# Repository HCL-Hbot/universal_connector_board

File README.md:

# Healthboth PCB Design
This document outlines the contribution to a PCB design for project Healthbot, which is part of the Health Concept Lab of HAN University of Applied Sciences. It is part of a semester 6 student project including 3 Embedded Systems Engineers and 4 Industrial Design Engineers. The goal for this project was developing a social robot for healthcare, with several functionalities. This PCB is made to be integrated in the robot, but also made quite universal, so it can be used in new robot designs. In the folder media, there are images of the PCB. Because this was a first version, please look at the recommendations below!

## Components
Some components on the PCB that were needed are the I/O Expander, voltage regulators and an UART multiplexer. 
  ### I/O Expander
  Because the GPIO pins of the Pico were completely full and we still needed some, we added an I/O Expander which works with I2C. This expander has 8 I/O channels,   which are also all connected. 
  ### Voltage regulators
  Because of the several needed voltages for the components, two regulators are on the PCB. There is 12 Volt coming in to the PCB via the block terminal. This is     guided to a TSR 1-2433, which converts it to 3.3V. Also a 5V regulator is on the PCB, which was more complicated because it has to have a high output current due   to the ledstrips needing lots of current. 
  ### UART Multiplexer
  The motor driver modules can be controlled via UART communication. Because the Pico doesn't have lots of UART channels, and are already needed for                  communication between the RPI4 and the Pico e.g., an UART Multiplexer was added. Although we don't use it to control our motor drivers, this is still a      possibility because of this multiplexer. This also provided the board with 2 extra UART possibilities for whatever component needs it. 

## !! Issues 
1) The 5V regulator did not work. It is not clear if the regulator wasn't solderded correctly, or the buck converter circuit was not working. Anyways, there was a short between GND and 12V somewhere around the regulator. 
2) Each display needs a identical reset line. The reset line is apparently used to to sync, or atleast stabilize, even though there are seperate chip select lines. 
3) We do not know if the UART multiplexer works, because we don't use it and we needed a pin from the Pico to resolve the previous issue (see Temporary solutions below).

### Temporary solutions
1) Because of safety and time shortage, we just left out the 5V regulator and its circuit that did not work. We now provide 5V via the extra Vcc pins that were added originally as voltage output pins.
2) We used the Pico GPIO pin 21 as extra reset line for the 2nd display. This was originally the 'INH' of the UART Multiplexer. See image below for the connection made. Here can be seen that the trace on the PCB from GPIO21 to the UART Mux was deliberately damaged and replaced with a connection to the reset pin of the 2nd display.

## Recommendations
Below are recommendations for the next group that gets to design a PCB for project Healthbot. These are additions to the previous named issues that need to be adjusted. These recommendations are up to the next developer to decide.

1) Add explicit header pins next to the PICO. This can be useful to easily attach external equipment like a Logic Analyzer or TTL-module, or simply wires to a breadboard if needed. (You can see in the picture of the PCB that we soldered them on for now).
2) Flip the display pin order. This is convenient for testing and prototyping, because the displays can than just be connected (temporarily) to headers on the PCB without the need for several cables. 
3) Add more silk layer documenation. Some of this was already actually done in the design, but some of these labels were skipped during production for some reason. (Also adding small hints for Vcc, gnd and other pins could be useful for connecting the components, when not using JST connectors).
4) Add a working 5V regulator, with enough output current (>6A). Try to not use a regulator that is too small, this was a problem in the first version. 
5) Add status LEDs and just an onboard LED to control.
6) Add a couple of buttons, like to reset the PICO for example. Also, power on/off buttons would be nice (could be tricky for the RPI, but would be useful).

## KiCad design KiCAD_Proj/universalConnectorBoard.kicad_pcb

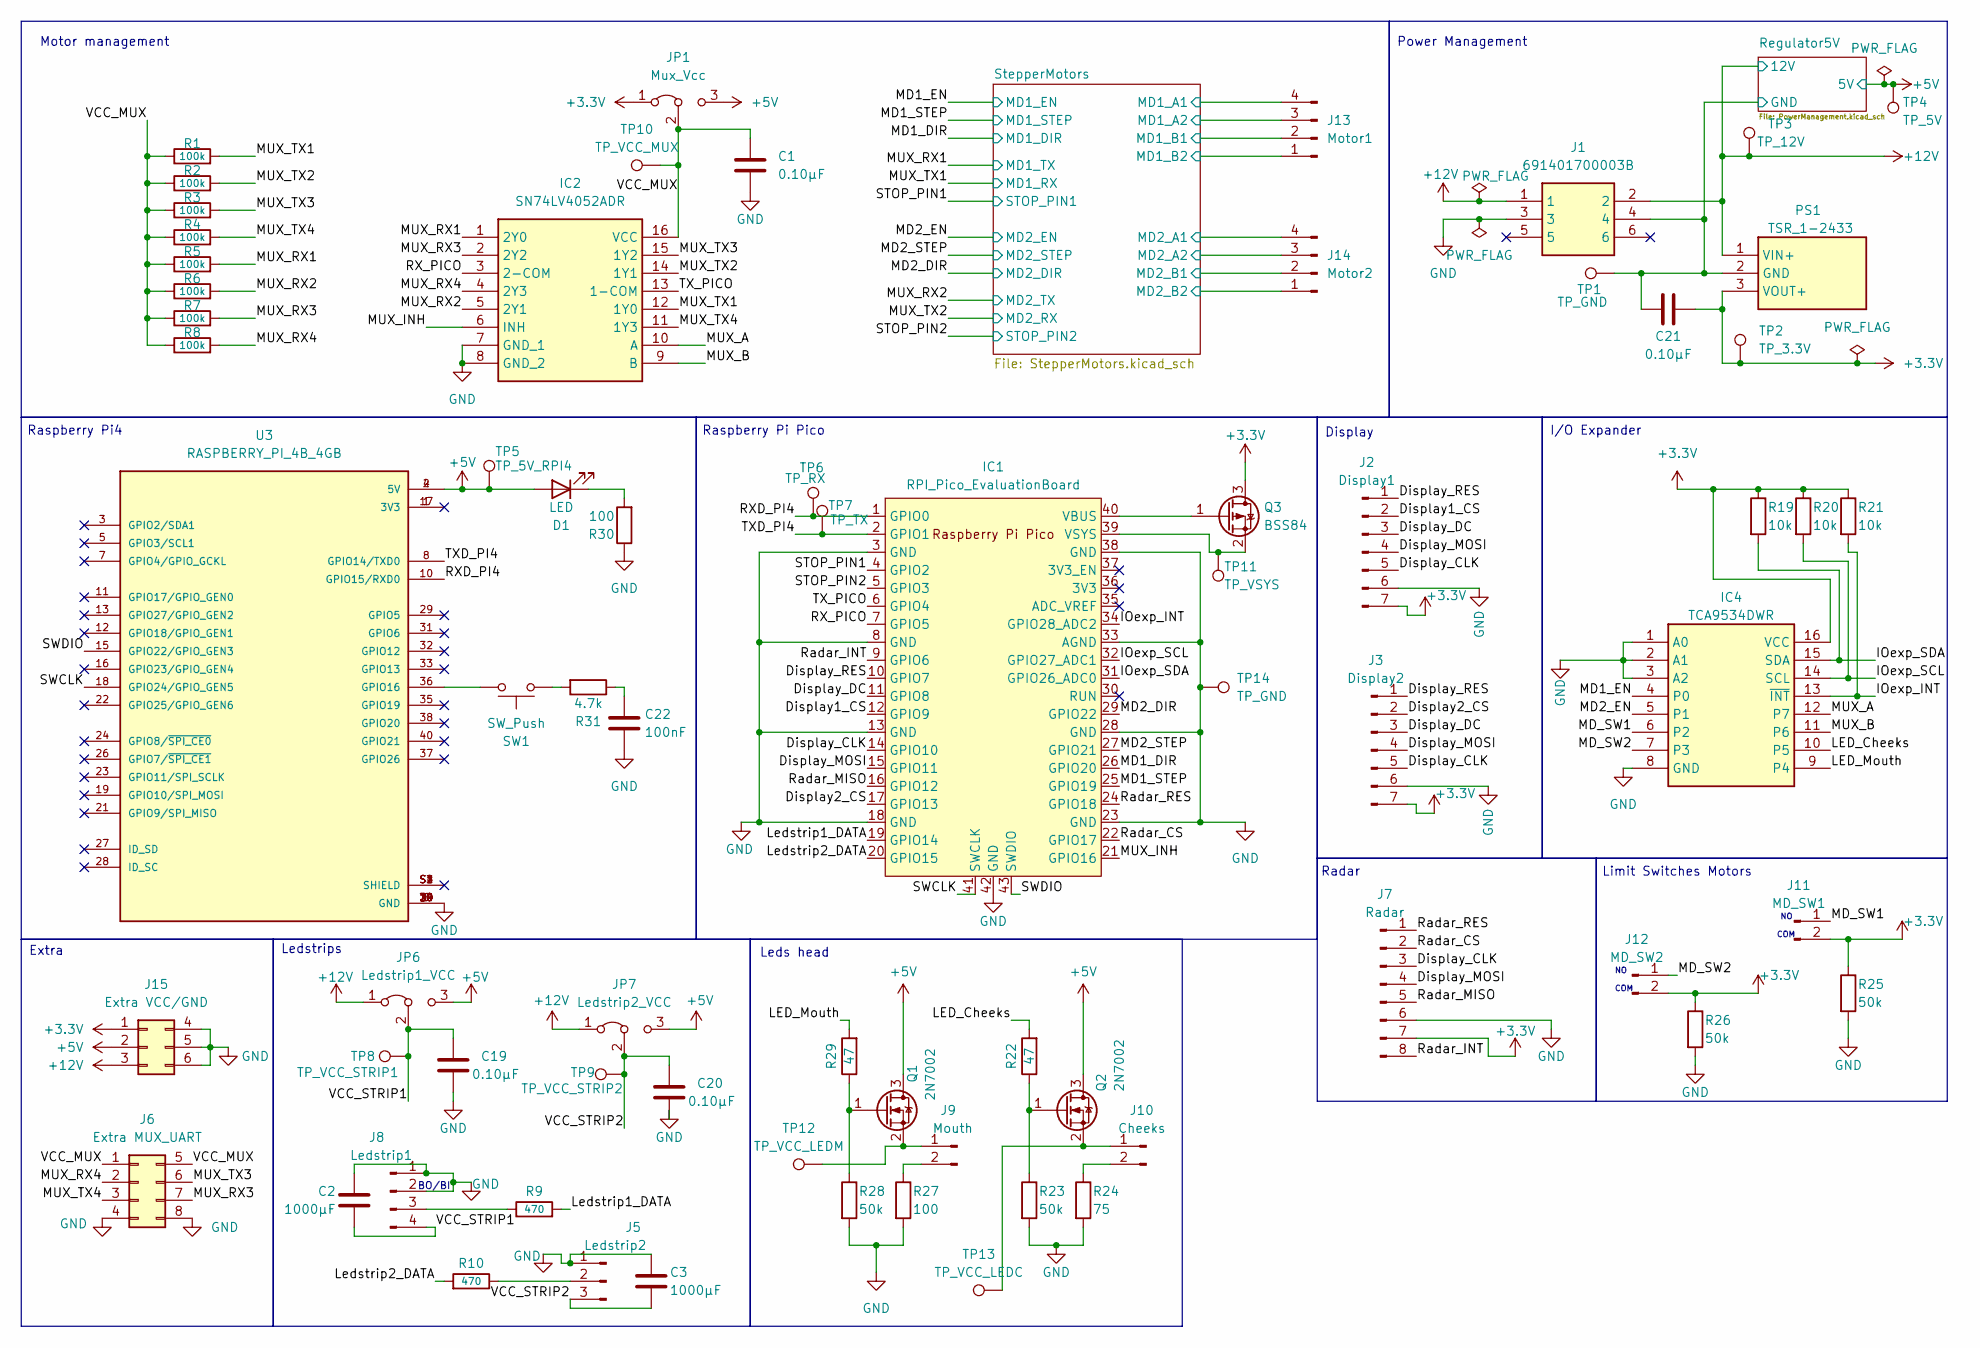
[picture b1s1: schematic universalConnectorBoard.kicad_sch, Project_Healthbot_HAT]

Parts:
C1, C19, C20, C21: 0.10μF; C_0603_1608Metric_Pad1.08x0.95mm_HandSolder
C2, C3: 1000μF; C_0603_1608Metric_Pad1.08x0.95mm_HandSolder
C22: 100nF; C_0603_1608Metric_Pad1.08x0.95mm_HandSolder
D1: LED; LED_0603_1608Metric_Pad1.05x0.95mm_HandSolder
IC1: RPI_Pico_EvaluationBoard; RPi_Pico_SMD_TH
IC2: SN74LV4052ADR; SOIC127P600X175-16N; Mouser Part Number 595-SN74LV4052ADR
IC4: TCA9534DWR; SOIC127P1030X265-16N; Mouser Part Number 595-TCA9534DWR
J1: 691401700003B; Manufacturer_Part_Number 691401700003B
J2: Display1; JST_XH_S7B-XH-A_1x07_P2.50mm_Horizontal
J3: Display2; JST_XH_S7B-XH-A_1x07_P2.50mm_Horizontal
J5: Ledstrip2; JST_XH_S3B-XH-A_1x03_P2.50mm_Horizontal
J6: Extra MUX_UART; PinHeader_2x04_P2.54mm_Vertical
J7: Radar; JST_XH_S8B-XH-A_1x08_P2.50mm_Horizontal
J8: Ledstrip1; JST_XH_S4B-XH-A_1x04_P2.50mm_Horizontal
J9: Mouth; JST_XH_S2B-XH-A_1x02_P2.50mm_Horizontal
J10: Cheeks; JST_XH_S2B-XH-A_1x02_P2.50mm_Horizontal
J11: MD_SW1; JST_XH_S2B-XH-A_1x02_P2.50mm_Horizontal
J12: MD_SW2; JST_XH_S2B-XH-A_1x02_P2.50mm_Horizontal
J13: Motor1; JST_XH_S4B-XH-A_1x04_P2.50mm_Horizontal
J14: Motor2; JST_XH_S4B-XH-A_1x04_P2.50mm_Horizontal
J15: Extra VCC/GND; PinHeader_2x03_P2.54mm_Vertical
JP1: Mux_Vcc; PinHeader_1x03_P2.54mm_Vertical
JP6: Ledstrip1_VCC; PinHeader_1x03_P2.54mm_Vertical
JP7: Ledstrip2_VCC; PinHeader_1x03_P2.54mm_Vertical
PS1: TSR_1-2433; TSR-1-2433; Manufacturer_Part_Number TSR 1-2433
Q1, Q2: 2N7002; SOT-23
Q3: BSS84; SOT-23
R1, R2, R3, R4, R5, R6, R7, R8: 100k; R_0603_1608Metric_Pad0.98x0.95mm_HandSolder
R9, R10: 470; R_0603_1608Metric_Pad0.98x0.95mm_HandSolder
R19, R20, R21: 10k; R_0603_1608Metric_Pad0.98x0.95mm_HandSolder
R22, R29: 47; R_0603_1608Metric_Pad0.98x0.95mm_HandSolder
R23, R25, R26, R28: 50k; R_0603_1608Metric_Pad0.98x0.95mm_HandSolder
R24: 75; R_0603_1608Metric_Pad0.98x0.95mm_HandSolder
R27, R30: 100; R_0603_1608Metric_Pad0.98x0.95mm_HandSolder
R31: 4.7k; R_0603_1608Metric_Pad0.98x0.95mm_HandSolder
SW1: SW_Push; PinHeader_1x02_P2.54mm_Vertical
TP1, TP14: TP_GND; TestPoint_Pad_D1.5mm
TP2: TP_3.3V; TestPoint_Pad_D1.5mm
TP3: TP_12V; TestPoint_Pad_D1.5mm
TP4: TP_5V; TestPoint_Pad_D1.5mm
TP5: TP_5V_RPI4; TestPoint_Pad_D1.5mm
TP6: TP_RX; TestPoint_Pad_D1.5mm
TP7: TP_TX; TestPoint_Pad_D1.5mm
TP8: TP_VCC_STRIP1; TestPoint_Pad_D1.5mm
TP9: TP_VCC_STRIP2; TestPoint_Pad_D1.5mm
TP10: TP_VCC_MUX; TestPoint_Pad_D1.5mm
TP11: TP_VSYS; TestPoint_Pad_D1.5mm
TP12: TP_VCC_LEDM; TestPoint_Pad_D1.5mm
TP13: TP_VCC_LEDC; TestPoint_Pad_D1.5mm
U3: RASPBERRY_PI_4B_4GB; MODULE_RASPBERRY_PI_4B_4GB; PARTREV 4

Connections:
+3.3V: C21.2, IC4.16 (VCC), J2.7, J3.7, J7.7, J11.2, J12.2, J15.1, JP1.1 (A), PS1.3 (VOUT+), Q3.3 (D), R19.1, R20.1, R21.1, R25.1, R26.1, TP2.1; also elsewhere on the board
+5V: D1.2 (A), J15.2, JP1.3 (B), JP6.3 (B), JP7.3 (B), Q1.3 (D), Q2.3 (D), TP4.1, TP5.1, U3.2 (5V), U3.4 (5V); also elsewhere on the board
+12V: J1.1, J1.2, J15.3, JP6.1 (A), JP7.1 (A), PS1.1 (VIN+), TP3.1; also elsewhere on the board
/Display1_CS: IC1.12 (GPIO9), J2.2
/Display2_CS: IC1.17 (GPIO13), J3.2
/Display_CLK: IC1.14 (GPIO10), J2.5, J3.5, J7.3
/Display_DC: IC1.11 (GPIO8), J2.3, J3.3
/Display_MOSI: IC1.15 (GPIO11), J2.4, J3.4, J7.4
/Display_RES: IC1.10 (GPIO7), J2.1, J3.1
/IOexp_INT: IC1.34 (GPIO28_ADC2), IC4.13 (~INT), R21.2
/IOexp_SCL: IC1.32 (GPIO27_ADC1), IC4.14 (SCL), R20.2
/IOexp_SDA: IC1.31 (GPIO26_ADC0), IC4.15 (SDA), R19.2
/LED_Cheeks: IC4.10 (P5), R22.2
/LED_Mouth: IC4.9 (P4), R29.2
/Ledstrip1_DATA: IC1.19 (GPIO14), R9.2
/Ledstrip2_DATA: IC1.20 (GPIO15), R10.2
/MD1_DIR: IC1.26 (GPIO20); also elsewhere on the board
/MD1_EN: IC4.4 (P0); also elsewhere on the board
/MD1_STEP: IC1.25 (GPIO19); also elsewhere on the board
/MD2_DIR: IC1.29 (GPIO22); also elsewhere on the board
/MD2_EN: IC4.5 (P1); also elsewhere on the board
/MD2_STEP: IC1.27 (GPIO21); also elsewhere on the board
/MD_SW1: IC4.6 (P2), J11.1
/MD_SW2: IC4.7 (P3), J12.1
/MUX_A: IC2.10 (A), IC4.12 (P7)
/MUX_B: IC2.9 (B), IC4.11 (P6)
/MUX_INH: IC1.21 (GPIO16), IC2.6 (INH)
/MUX_RX1: IC2.1 (2Y0), R5.2; also elsewhere on the board
/MUX_RX2: IC2.5 (2Y1), R6.2; also elsewhere on the board
/MUX_RX3: IC2.2 (2Y2), J6.7, R7.2
/MUX_RX4: IC2.4 (2Y3), J6.2, R8.2
/MUX_TX1: IC2.12 (1Y0), R1.2; also elsewhere on the board
/MUX_TX2: IC2.14 (1Y1), R2.2; also elsewhere on the board
/MUX_TX3: IC2.15 (1Y2), J6.6, R3.2
/MUX_TX4: IC2.11 (1Y3), J6.3, R4.2
/RXD_PI4: IC1.1 (GPIO0), TP6.1, U3.10 (GPIO15/RXD0)
/RX_PICO: IC1.7 (GPIO5), IC2.3 (2-COM)
/Radar_CS: IC1.22 (GPIO17), J7.2
/Radar_INT: IC1.9 (GPIO6), J7.8
/Radar_MISO: IC1.16 (GPIO12), J7.5
/Radar_RES: IC1.24 (GPIO18), J7.1
/STOP_PIN1: IC1.4 (GPIO2); also elsewhere on the board
/STOP_PIN2: IC1.5 (GPIO3); also elsewhere on the board
/SWCLK: IC1.41 (SWCLK), U3.18 (GPIO24/GPIO_GEN5)
/SWDIO: IC1.43 (SWDIO), U3.15 (GPIO22/GPIO_GEN3)
/StepperMotors/MD1_A1: J13.4; also elsewhere on the board
/StepperMotors/MD1_A2: J13.3; also elsewhere on the board
/StepperMotors/MD1_B1: J13.2; also elsewhere on the board
/StepperMotors/MD1_B2: J13.1; also elsewhere on the board
/StepperMotors/MD2_A1: J14.4; also elsewhere on the board
/StepperMotors/MD2_A2: J14.3; also elsewhere on the board
/StepperMotors/MD2_B1: J14.2; also elsewhere on the board
/StepperMotors/MD2_B2: J14.1; also elsewhere on the board
/TXD_PI4: IC1.2 (GPIO1), TP7.1, U3.8 (GPIO14/TXD0)
/TX_PICO: IC1.6 (GPIO4), IC2.13 (1-COM)
/VCC_MUX: C1.1, IC2.16 (VCC), J6.1, J6.5, JP1.2 (C), R1.1, R2.1, R3.1, R4.1, R5.1, R6.1, R7.1, R8.1, TP10.1
/VCC_STRIP1: C2.2, C19.1, J8.4, JP6.2 (C), TP8.1
/VCC_STRIP2: C3.2, C20.1, J5.3, JP7.2 (C), TP9.1
GND: C1.2, C2.1, C3.1, C19.2, C20.2, C21.1, C22.2, IC1.3 (GND), IC1.8 (GND), IC1.13 (GND), IC1.18 (GND), IC1.23 (GND), IC1.28 (GND), IC1.33 (AGND), IC1.38 (GND), IC1.42 (GND), IC2.7 (GND_1), IC2.8 (GND_2), IC4.1 (A0), IC4.2 (A1), IC4.3 (A2), IC4.8 (GND), J1.3, J1.4, J2.6, J3.6, J5.1, J6.4, J6.8, J7.6, J8.1, J8.2, J15.4, J15.5, J15.6, PS1.2 (GND), R23.2, R24.2, R25.2, R26.2, R27.2, R28.2, R30.1, TP1.1, TP14.1, U3.6 (GND), U3.9 (GND), U3.14 (GND), U3.20 (GND), U3.25 (GND), U3.30 (GND), U3.34 (GND), U3.39 (GND); also elsewhere on the board
unnamed: C22.1, R31.1
unnamed: D1.1 (K), R30.2
unnamed: IC1.40 (VBUS), Q3.1 (G)
unnamed: IC1.39 (VSYS), Q3.2 (S), TP11.1
unnamed: J5.2, R10.1
unnamed: J8.3, R9.1
unnamed: J9.1, Q1.2 (S), TP12.1
unnamed: J9.2, R27.1
unnamed: J10.1, Q2.2 (S), TP13.1
unnamed: J10.2, R24.1
unnamed: Q1.1 (G), R28.1, R29.1
unnamed: Q2.1 (G), R22.1, R23.1
unnamed: R31.2, SW1.1
unnamed: SW1.2, U3.36 (GPIO16)

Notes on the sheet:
Display
Motor management
Raspberry Pi Pico
Power Management
BO/BI
Limit Switches Motors
COM
Raspberry Pi4
Ledstrips
Leds head
Radar
I/O Expander
Extra

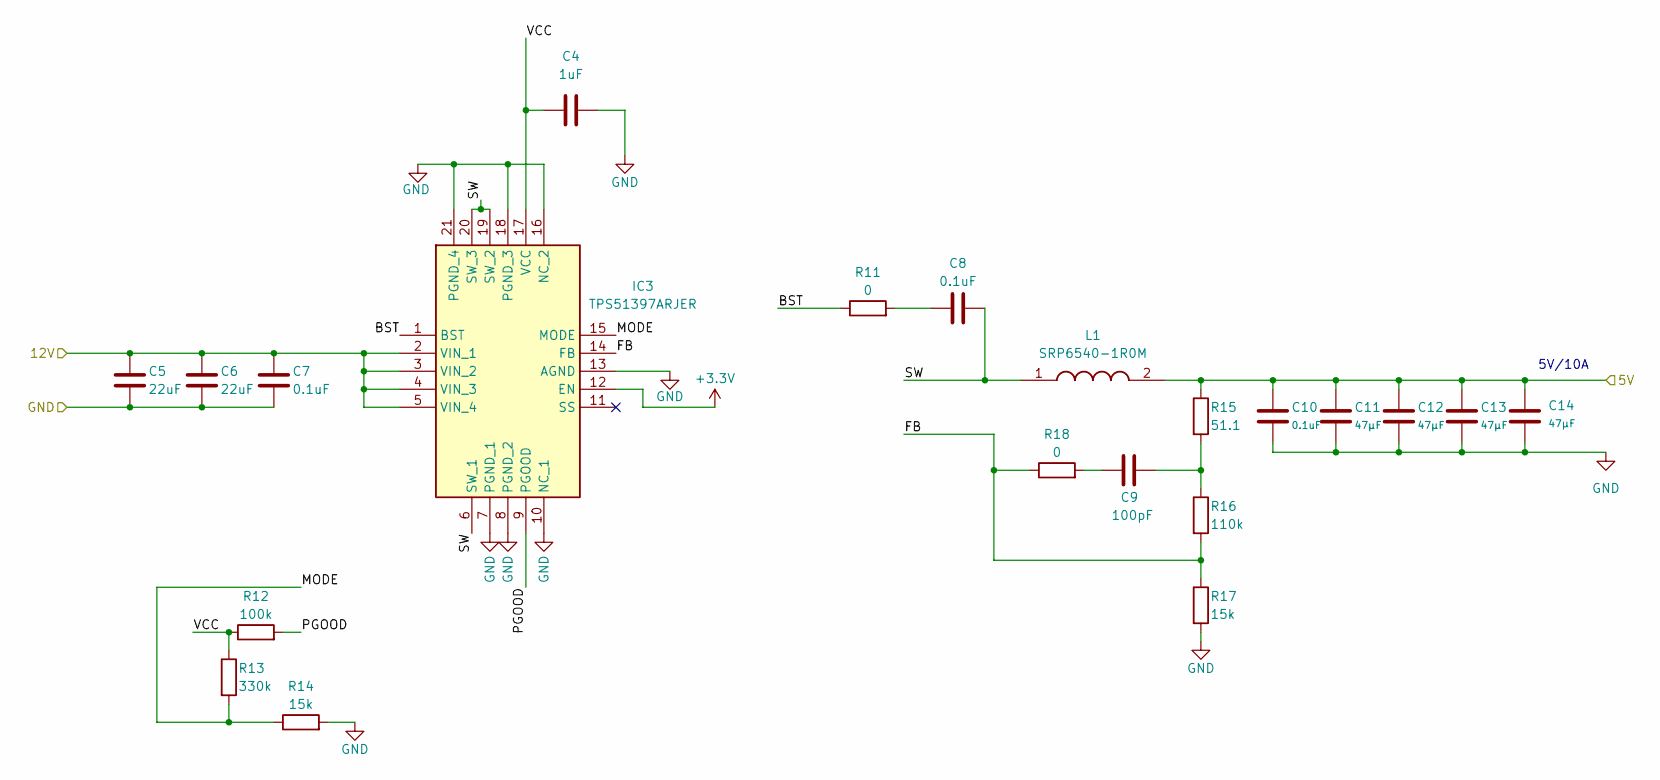
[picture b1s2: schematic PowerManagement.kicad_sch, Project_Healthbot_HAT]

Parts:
C4: 1uF; C_0603_1608Metric_Pad1.08x0.95mm_HandSolder
C5, C6: 22uF; C_0603_1608Metric_Pad1.08x0.95mm_HandSolder
C7, C8, C10: 0.1uF; C_0603_1608Metric_Pad1.08x0.95mm_HandSolder
C9: 100pF; C_0603_1608Metric_Pad1.08x0.95mm_HandSolder
C11, C12, C13, C14: 47µF; C_0603_1608Metric_Pad1.08x0.95mm_HandSolder
IC3: TPS51397ARJER; QFN45P300X300X100-21N-D; Mouser Part Number 595-TPS51397ARJER
L1: SRP6540-1R0M; INDPM7265X400N; Manufacturer_Part_Number SRP6540-1R0M
R11, R18: 0; R_0603_1608Metric_Pad0.98x0.95mm_HandSolder
R12: 100k; R_0603_1608Metric_Pad0.98x0.95mm_HandSolder
R13: 330k; R_0603_1608Metric_Pad0.98x0.95mm_HandSolder
R14, R17: 15k; R_0603_1608Metric_Pad0.98x0.95mm_HandSolder
R15: 51.1; R_0603_1608Metric_Pad0.98x0.95mm_HandSolder
R16: 110k; R_0603_1608Metric_Pad0.98x0.95mm_HandSolder

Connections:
+3.3V: IC3.12 (EN); also elsewhere on the board
+5V: C10.1, C11.1, C12.1, C13.1, C14.1, L1.2, R15.1; also elsewhere on the board
+12V: C5.1, C6.1, C7.1, IC3.2 (VIN_1), IC3.3 (VIN_2), IC3.4 (VIN_3), IC3.5 (VIN_4); also elsewhere on the board
/Regulator5V/BST: IC3.1 (BST), R11.1
/Regulator5V/FB: IC3.14 (FB), R16.2, R17.1, R18.1
/Regulator5V/MODE: IC3.15 (MODE), R13.2, R14.1
/Regulator5V/PGOOD: IC3.9 (PGOOD), R12.2
/Regulator5V/SW: C8.2, IC3.6 (SW_1), IC3.19 (SW_2), IC3.20 (SW_3), L1.1
/Regulator5V/VCC: C4.1, IC3.17 (VCC), R12.1, R13.1
GND: C4.2, C5.2, C6.2, C7.2, C10.2, C11.2, C12.2, C13.2, C14.2, IC3.7 (PGND_1), IC3.8 (PGND_2), IC3.10 (NC_1), IC3.13 (AGND), IC3.16 (NC_2), IC3.18 (PGND_3), IC3.21 (PGND_4), R14.2, R17.2; also elsewhere on the board
unnamed: C8.1, R11.2
unnamed: C9.1, R15.2, R16.1
unnamed: C9.2, R18.2

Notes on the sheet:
5V/10A

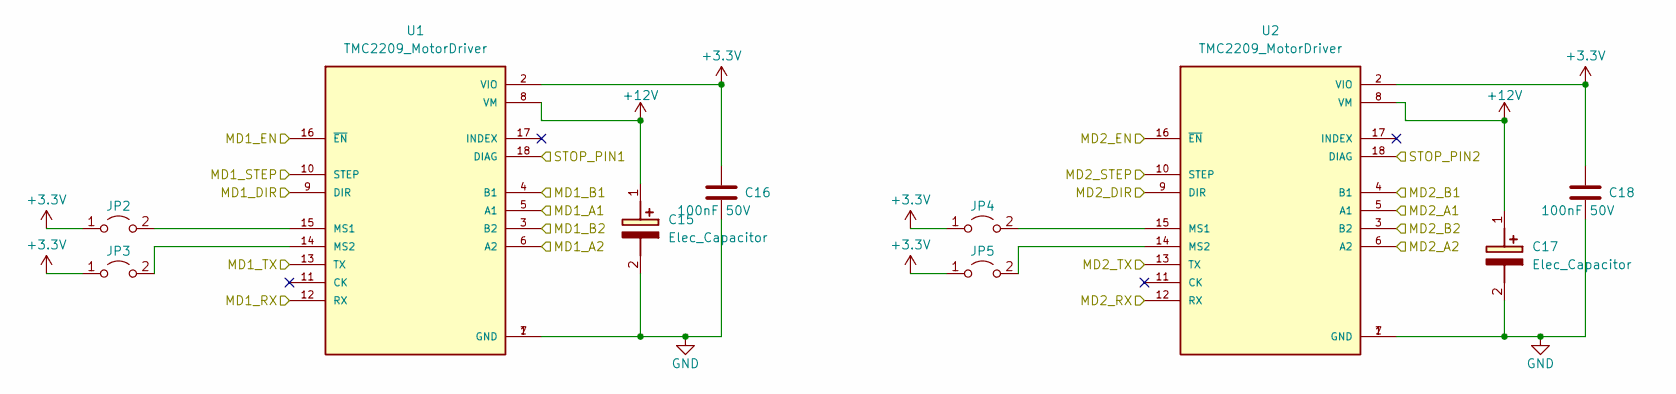
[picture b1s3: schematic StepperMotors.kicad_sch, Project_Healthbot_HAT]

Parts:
C15, C17: Elec_Capacitor; CAPAE1000X1050N; Mouser Part Number 594-MAL214699103E3
C16, C18: 100nF 50V; C_0603_1608Metric_Pad1.08x0.95mm_HandSolder; LCSC C476766
JP2, JP3, JP4, JP5: Jumper_2_Open; SolderJumper-2_P1.3mm_Open_RoundedPad1.0x1.5mm; LCSC x
U1, U2: TMC2209_MotorDriver; MODULE_TMC2209_SILENTSTEPSTICK; PARTREV 1.20

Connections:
+3.3V: C16.1, C18.1, JP2.1 (A), JP3.1 (A), JP4.1 (A), JP5.1 (A), U1.2 (VIO), U2.2 (VIO); also elsewhere on the board
+12V: C15.1 (+), C17.1 (+), U1.8 (VM), U2.8 (VM); also elsewhere on the board
/MD1_DIR: U1.9 (DIR); also elsewhere on the board
/MD1_EN: U1.16 (~EN); also elsewhere on the board
/MD1_STEP: U1.10 (STEP); also elsewhere on the board
/MD2_DIR: U2.9 (DIR); also elsewhere on the board
/MD2_EN: U2.16 (~EN); also elsewhere on the board
/MD2_STEP: U2.10 (STEP); also elsewhere on the board
/MUX_RX1: U1.13 (TX); also elsewhere on the board
/MUX_RX2: U2.13 (TX); also elsewhere on the board
/MUX_TX1: U1.12 (RX); also elsewhere on the board
/MUX_TX2: U2.12 (RX); also elsewhere on the board
/STOP_PIN1: U1.18 (DIAG); also elsewhere on the board
/STOP_PIN2: U2.18 (DIAG); also elsewhere on the board
/StepperMotors/MD1_A1: U1.5 (A1); also elsewhere on the board
/StepperMotors/MD1_A2: U1.6 (A2); also elsewhere on the board
/StepperMotors/MD1_B1: U1.4 (B1); also elsewhere on the board
/StepperMotors/MD1_B2: U1.3 (B2); also elsewhere on the board
/StepperMotors/MD2_A1: U2.5 (A1); also elsewhere on the board
/StepperMotors/MD2_A2: U2.6 (A2); also elsewhere on the board
/StepperMotors/MD2_B1: U2.4 (B1); also elsewhere on the board
/StepperMotors/MD2_B2: U2.3 (B2); also elsewhere on the board
GND: C15.2 (-), C16.2, C17.2 (-), C18.2, U1.1 (GND), U1.7 (GND), U2.1 (GND), U2.7 (GND); also elsewhere on the board
unnamed: JP2.2 (B), U1.15 (MS1)
unnamed: JP3.2 (B), U1.14 (MS2)
unnamed: JP4.2 (B), U2.15 (MS1)
unnamed: JP5.2 (B), U2.14 (MS2)

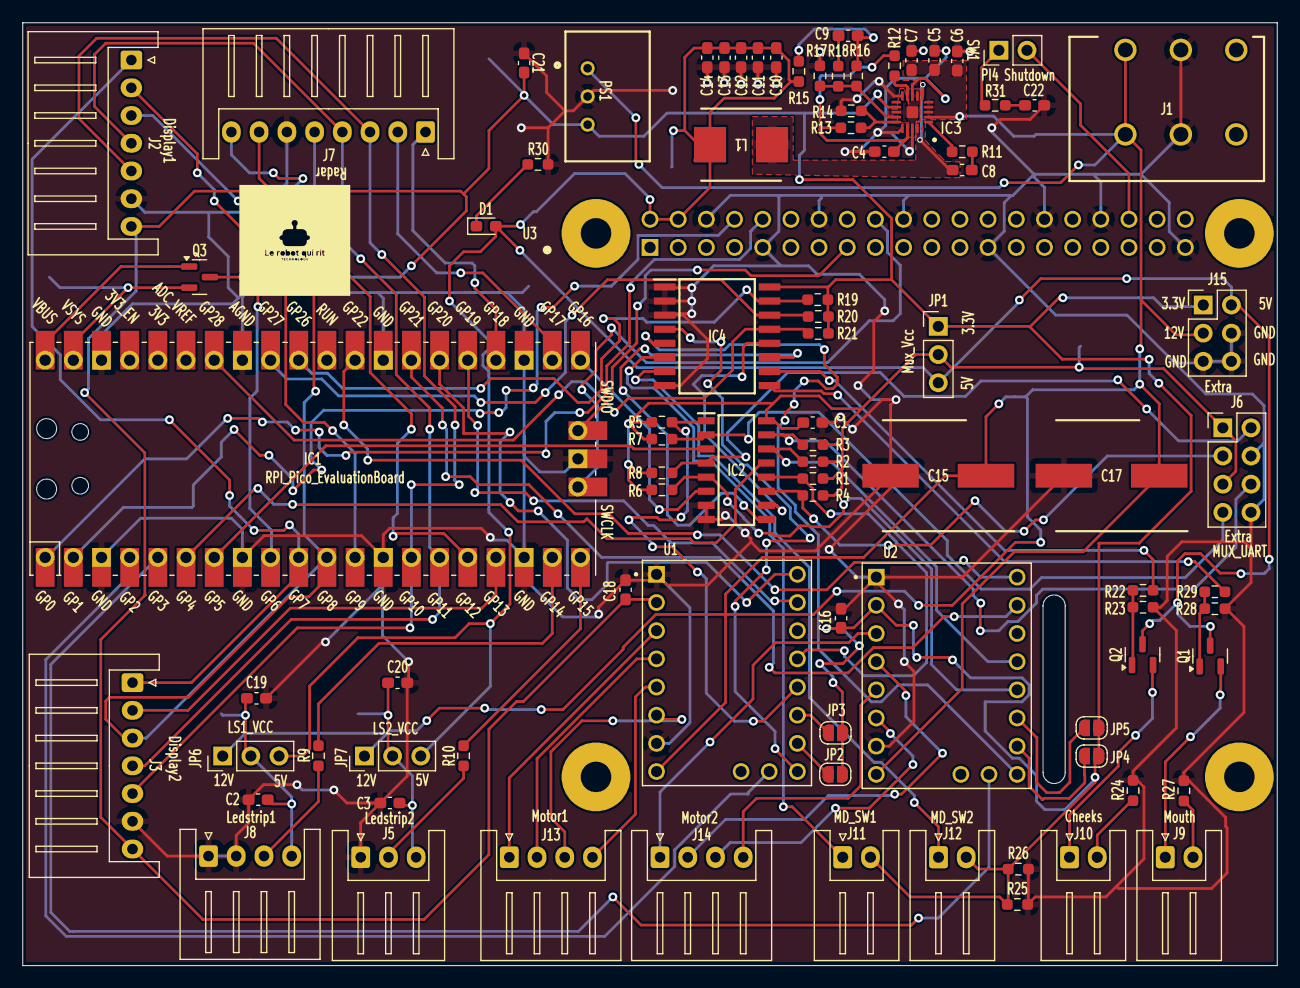
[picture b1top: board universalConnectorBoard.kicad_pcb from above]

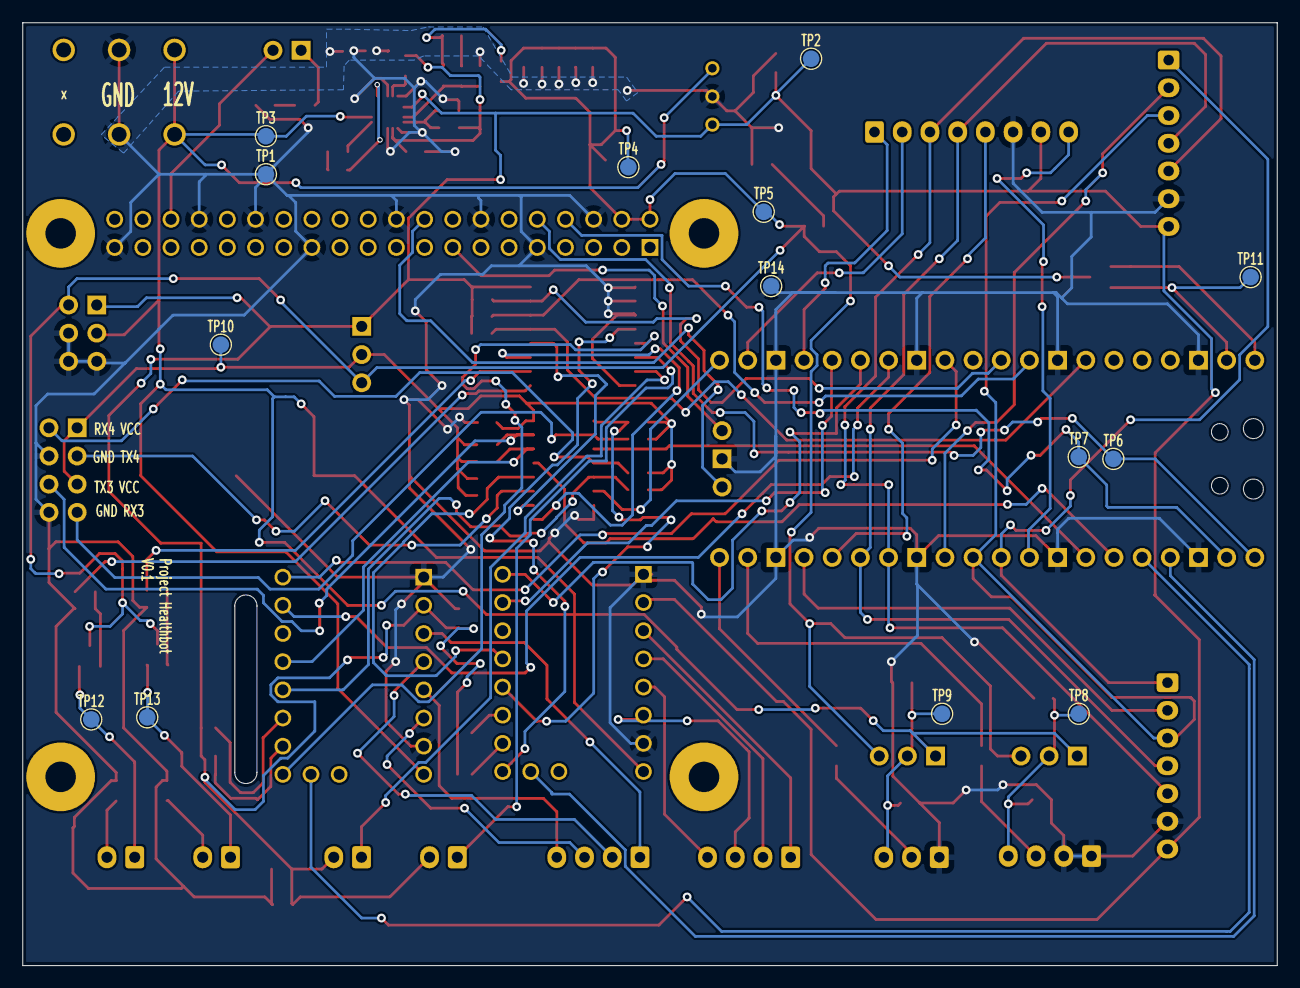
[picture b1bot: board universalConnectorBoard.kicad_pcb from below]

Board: 2 copper layers, 113.1 x 85.0 mm, 103 parts (14 on the bottom side), 86 nets.

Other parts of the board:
Logo: d0ed0aed-a5b7-4fbb-959d-d2596cb26e0d

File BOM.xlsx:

Reference, | Value | , | Datasheet | , | Footprint | , | Qty | , | DNP | , | Beschrijving
C1,C19,C20,C21, | 0.10Î¼F | , | ~ | , | Capacitor_SMD:C_0603_1608Metric_Pad1.08x0.95mm_HandSolder | , | 4 | , |  | ,
C2,C3, | 1000Î¼F | , | ~ | , | Capacitor_SMD:C_0603_1608Metric_Pad1.08x0.95mm_HandSolder | , | 2 | , |  | ,
C4, | 1uF | , | ~ | , | Capacitor_SMD:C_0603_1608Metric_Pad1.08x0.95mm_HandSolder | , | 1 | , |  | ,
C5,C6, | 22uF | , | ~ | , | Capacitor_SMD:C_0603_1608Metric_Pad1.08x0.95mm_HandSolder | , | 2 | , |  | ,
C7,C8,C10, | 0.1uF | , | ~ | , | Capacitor_SMD:C_0603_1608Metric_Pad1.08x0.95mm_HandSolder | , | 3 | , |  | ,
C9, | 100pF | , | ~ | , | Capacitor_SMD:C_0603_1608Metric_Pad1.08x0.95mm_HandSolder | , | 1 | , |  | ,
C11,C12,C13,C14, | 47ÂµF | , | ~ | , | Capacitor_SMD:C_0603_1608Metric_Pad1.08x0.95mm_HandSolder | , | 4 | , |  | ,
C15,C17, | Elec_Capacitor | , | https://www.vishay.com/docs/28403/146cti.pdf | , | SamacSys_Parts:CAPAE1000X1050N | , | 2 | , |  | , | Vishay Extreme 100uF 50 V Aluminium Electrolytic Capacitor 1010, 146 CTI Series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
C16,C18, | 100nF 50V | , | ~ | , | Capacitor_SMD:C_0603_1608Metric_Pad1.08x0.95mm_HandSolder | , | 2 | , |  | ,
C22, | 100nF | , | ~ | , | Capacitor_SMD:C_0603_1608Metric_Pad1.08x0.95mm_HandSolder | , | 1 | , |  | , | Unpolarized capacitor
D1, | LED | , | ~ | , | LED_SMD:LED_0603_1608Metric_Pad1.05x0.95mm_HandSolder | , | 1 | , |  | ,
IC1, | RPI_Pico_EvaluationBoard | , | https://datasheets.raspberrypi.com/pico/pico-datasheet.pdf | , | Healthbot-Footprints:RPi_Pico_SMD_TH | , | 1 | , |  | , | Raspberry Pi Pico W board
IC2, | SN74LV4052ADR | , | http://www.ti.com/lit/gpn/sn74lv4052a | , | Healthbot-Footprints:SOIC127P600X175-16N | , | 1 | , |  | ,
IC3, | TPS51397ARJER | , | https://www.ti.com/lit/gpn/tps51397a?HQS=ti-null-null-sf-df-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 | , | Healthbot-Footprints:QFN45P300X300X100-21N-D | , | 1 | , |  | ,
IC4, | TCA9534DWR | , | http://www.ti.com/lit/gpn/tca9534 | , | SamacSys_Parts:SOIC127P1030X265-16N | , | 1 | , |  | ,
J1, | 691401700003B | , | http://katalog.we-online.de/em/datasheet/6914017000xxB.pdf | , | SamacSys_Parts:691401700003B | , | 1 | , |  | , | Wurth Elektronik, 401B 5mm Pitch, 3 Way PCB Terminal Block
J2, | Display1 | , | ~ | , | Connector_JST:JST_XH_S7B-XH-A_1x07_P2.50mm_Horizontal | , | 1 | , |  | ,
J3, | Display2 | , | ~ | , | Connector_JST:JST_XH_S7B-XH-A_1x07_P2.50mm_Horizontal | , | 1 | , |  | ,
J5, | Ledstrip2 | , | ~ | , | Connector_JST:JST_XH_S3B-XH-A_1x03_P2.50mm_Horizontal | , | 1 | , |  | ,
J6, | Extra MUX_UART | , | ~ | , | Connector_PinHeader_2.54mm:PinHeader_2x04_P2.54mm_Vertical | , | 1 | , |  | ,
J7, | Radar | , | ~ | , | Connector_JST:JST_XH_S8B-XH-A_1x08_P2.50mm_Horizontal | , | 1 | , |  | , | Generic connector, single row, 01x08, script generated
J8, | Ledstrip1 | , | ~ | , | Connector_JST:JST_XH_S4B-XH-A_1x04_P2.50mm_Horizontal | , | 1 | , |  | ,
J9, | Mouth | , | ~ | , | Connector_JST:JST_XH_S2B-XH-A_1x02_P2.50mm_Horizontal | , | 1 | , |  | ,
J10, | Cheeks | , | ~ | , | Connector_JST:JST_XH_S2B-XH-A_1x02_P2.50mm_Horizontal | , | 1 | , |  | ,
J11, | MD_SW1 | , | ~ | , | Connector_JST:JST_XH_S2B-XH-A_1x02_P2.50mm_Horizontal | , | 1 | , |  | ,
J12, | MD_SW2 | , | ~ | , | Connector_JST:JST_XH_S2B-XH-A_1x02_P2.50mm_Horizontal | , | 1 | , |  | ,
J13, | Motor1 | , | ~ | , | Connector_JST:JST_XH_S4B-XH-A_1x04_P2.50mm_Horizontal | , | 1 | , |  | ,
J14, | Motor2 | , | ~ | , | Connector_JST:JST_XH_S4B-XH-A_1x04_P2.50mm_Horizontal | , | 1 | , |  | ,
J15, | Extra VCC/GND | , | ~ | , | Connector_PinHeader_2.54mm:PinHeader_2x03_P2.54mm_Vertical | , | 1 | , |  | ,
JP1, | Mux_Vcc | , | ~ | , | Connector_PinHeader_2.54mm:PinHeader_1x03_P2.54mm_Vertical | , | 1 | , |  | ,
JP2,JP3,JP4,JP5, | Jumper_2_Open | , | ~ | , | Jumper:SolderJumper-2_P1.3mm_Open_RoundedPad1.0x1.5mm | , | 4 | , |  | ,
JP6, | Ledstrip1_VCC | , | ~ | , | Connector_PinHeader_2.54mm:PinHeader_1x03_P2.54mm_Vertical | , | 1 | , |  | ,
JP7, | Ledstrip2_VCC | , | ~ | , | Connector_PinHeader_2.54mm:PinHeader_1x03_P2.54mm_Vertical | , | 1 | , |  | ,
L1, | SRP6540-1R0M | , | https://www.bourns.com/docs/Product-Datasheets/SRP6540.pdf | , | Healthbot-Footprints:INDPM7265X400N | , | 1 | , |  | , | Bourns SRP6540 Series Shielded Wire-wound SMD Inductor with a Iron Core, 1 uH +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
PS1, | TSR_1-2433 | , | https://tracopower.com/tsr1-datasheet/ | , | Healthbot-Footprints:TSR-1-2433 | , | 1 | , |  | , | 1 Amp POL switching regulator, 4.6 to -36 VDC input, pos.-pos. circuit, LM78 co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
Q1,Q2, | 2N7002 | , | https://www.onsemi.com/pub/Collateral/NDS7002A-D.PDF | , | Package_TO_SOT_SMD:SOT-23 | , | 2 | , |  | , | 0.115A Id, 60V Vds, N-Channel MOSFET, SOT-23
Q3, | BSS84 | , | http://assets.nexperia.com/documents/data-sheet/BSS84.pdf | , | Package_TO_SOT_SMD:SOT-23 | , | 1 | , |  | , | -0.13A Id, -50V Vds, P-Channel MOSFET, SOT-23
R1,R2,R3,R4,R5,R6,R7,R8,R12, | 100k | , | ~ | , | Resistor_SMD:R_0603_1608Metric_Pad0.98x0.95mm_HandSolder | , | 9 | , |  | ,
R9,R10, | 470 | , | ~ | , | Resistor_SMD:R_0603_1608Metric_Pad0.98x0.95mm_HandSolder | , | 2 | , |  | ,
R11,R18, | 0 | , | ~ | , | Resistor_SMD:R_0603_1608Metric_Pad0.98x0.95mm_HandSolder | , | 2 | , |  | ,
R13, | 330k | , | ~ | , | Resistor_SMD:R_0603_1608Metric_Pad0.98x0.95mm_HandSolder | , | 1 | , |  | ,
R14,R17, | 15k | , | ~ | , | Resistor_SMD:R_0603_1608Metric_Pad0.98x0.95mm_HandSolder | , | 2 | , |  | ,
R15, | 51.1 | , | ~ | , | Resistor_SMD:R_0603_1608Metric_Pad0.98x0.95mm_HandSolder | , | 1 | , |  | ,
R16, | 110k | , | ~ | , | Resistor_SMD:R_0603_1608Metric_Pad0.98x0.95mm_HandSolder | , | 1 | , |  | ,
R19,R20,R21, | 10k | , | ~ | , | Resistor_SMD:R_0603_1608Metric_Pad0.98x0.95mm_HandSolder | , | 3 | , |  | ,
R22,R29, | 47 | , | ~ | , | Resistor_SMD:R_0603_1608Metric_Pad0.98x0.95mm_HandSolder | , | 2 | , |  | ,
R23,R25,R26,R28, | 50k | , | ~ | , | Resistor_SMD:R_0603_1608Metric_Pad0.98x0.95mm_HandSolder | , | 4 | , |  | ,
R24, | 75 | , | ~ | , | Resistor_SMD:R_0603_1608Metric_Pad0.98x0.95mm_HandSolder | , | 1 | , |  | ,
R27,R30, | 100 | , | ~ | , | Resistor_SMD:R_0603_1608Metric_Pad0.98x0.95mm_HandSolder | , | 2 | , |  | ,
R31, | 4.7k | , | ~ | , | Resistor_SMD:R_0603_1608Metric_Pad0.98x0.95mm_HandSolder | , | 1 | , |  | , | Resistor
SW1, | SW_Push | , | ~ | , | Connector_PinHeader_2.54mm:PinHeader_1x02_P2.54mm_Vertical | , | 1 | , |  | ,
TP2, | TP_3.3V | , | ~ | , | TestPoint:TestPoint_Pad_D1.5mm | , | 1 | , |  | , | test point
TP3, | TP_12V | , | ~ | , | TestPoint:TestPoint_Pad_D1.5mm | , | 1 | , |  | , | test point
TP4, | TP_5V | , | ~ | , | TestPoint:TestPoint_Pad_D1.5mm | , | 1 | , |  | , | test point
TP5,TP14, | TP_GND | , | ~ | , | TestPoint:TestPoint_Pad_D1.5mm | , | 2 | , |  | , | test point
TP6, | TP_RX | , | ~ | , | TestPoint:TestPoint_Pad_D1.5mm | , | 1 | , |  | , | test point
TP7, | TP_TX | , | ~ | , | TestPoint:TestPoint_Pad_D1.5mm | , | 1 | , |  | , | test point
TP8, | TP_VCC_STRIP1 | , | ~ | , | TestPoint:TestPoint_Pad_D1.5mm | , | 1 | , |  | , | test point
TP9, | TP_VCC_STRIP2 | , | ~ | , | TestPoint:TestPoint_Pad_D1.5mm | , | 1 | , |  | , | test point
TP10, | TP_VCC_MUX | , | ~ | , | TestPoint:TestPoint_Pad_D1.5mm | , | 1 | , |  | , | test point
TP11, | TP_VSYS | , | ~ | , | TestPoint:TestPoint_Pad_D1.5mm | , | 1 | , |  | , | test point
TP12, | TP_VCC_LEDM | , | ~ | , | TestPoint:TestPoint_Pad_D1.5mm | , | 1 | , |  | , | test point
TP13, | TP_VCC_LEDC | , | ~ | , | TestPoint:TestPoint_Pad_D1.5mm | , | 1 | , |  | , | test point
TP15, | TP_5V_RPI4 | , | ~ | , | TestPoint:TestPoint_Pad_D1.5mm | , | 1 | , |  | , | test point
U1,U2, | TMC2209_MotorDriver | , | https://www.analog.com/media/en/technical-documentation/data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 | , | Healthbot-Footprints:MODULE_TMC2209_SILENTSTEPSTICK | , | 2 | , |  | , | TMC2209 Motor Controller/Driver Power Management Evaluation Board
U3, | RASPBERRY_PI_4B_4GB | , |  | , | Healthbot-Footprints:MODULE_RASPBERRY_PI_4B_4GB | , | 1 | , |  | ,

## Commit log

2024-04-19 Add initial project folder structure, with seperate kicad project library.
2024-04-19 Added footprints
2024-04-20 Add pico board footprint with through-hole and smd in one, just found it and thought it is something for the PCB.
2024-04-24 Added several components and connections
2024-04-24 Added more components
2024-04-26 Multiple additions
2024-04-26 Added lots of connections
2024-05-08 All pico GPIO pins assigned
2024-05-08 Added excel sheet for overview of pin connections
2024-05-08 Excel adjustion
2024-05-15 Added power management
2024-05-16 Schematic nearly done, ordened
2024-05-16 Added new sheet for motors
2024-05-17 Finished schematic, in review
2024-05-17 -add missing connections in schematic, and some other small changes
2024-05-22 Schematic finished
2024-05-22 Added Pi HAT reference footprint
2024-05-23 Added RPI4 footprint + headers, start of pcb designer
2024-05-24 All components placed
2024-05-24 Minor movements
2024-05-24 PCB Design halfway
2024-05-24 Nearly finished, just some DRC Errors te check
2024-05-24 Added name on PCB....
2024-05-26 Finished!
2024-05-26 Added all neccessary files for ordering
2024-05-26 Added generated BOM file (as excel, csv did not commit
2024-05-26 Moved files folder
2024-05-29 Final version
2024-06-05 Changed connections excel sheet
2024-06-13 Added media
